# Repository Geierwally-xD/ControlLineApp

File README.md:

# ControlLineApp
Geierwally's stroke engine throttle control application for controlled line model planes

- Realizes full throttle control over control lines
- optional automatic flight position depended throttle control
- flight position sensor = MPU 6050 gyroscope accelerometer unit
- optional functions like retractable landing gear

- Hardware PCB design included, done with KiCad 8.0

- Full Software project included, done for Arduino Nano with VS Code and PlatformIO (optional Arduino IDE)
- See short video clip of position control and landing gear with landing light:
https://www.youtube.com/watch?v=91i4-DDLWDE

Geierwally's Verbrennungsmotor- Drosselvergasersteuerung für Fesselflugmodelle

- Drosselvergaser - Steuerung über Steuerdrähte mit optional automatischer Regelung über Fluglageerkennung
- Fluglagenerkennung über MPU 6050 Gyroskop Accelerometer - Einheit
- Optionale Funktionen wie Einziehfahrwerk

- Komplettes Hardware Platinenlayout enthalten, mit KiCad 8.0 entflochten

- Komplettes Software Projekt enthalten, für  Arduino Nano, entwickelt mit VS Code und PlatformIO (optional Arduino IDE)
- Kurzer Videoclip zeigt Regelung über Fluglage sowie Einziehfahrwerk und Landescheinwerfer:
https://www.youtube.com/watch?v=91i4-DDLWDE

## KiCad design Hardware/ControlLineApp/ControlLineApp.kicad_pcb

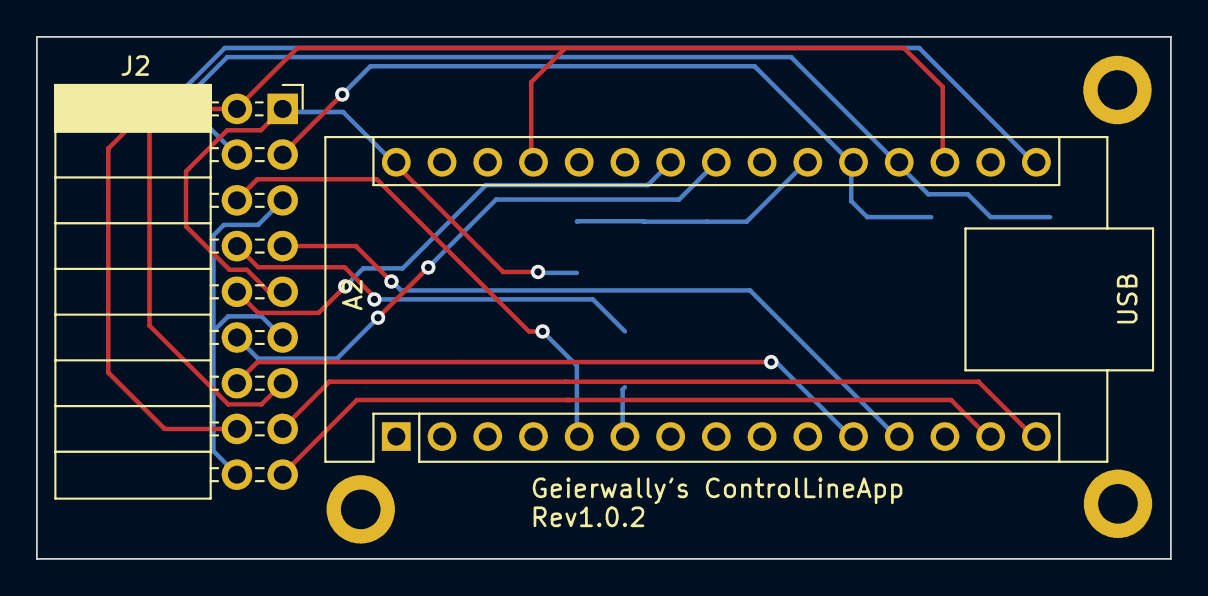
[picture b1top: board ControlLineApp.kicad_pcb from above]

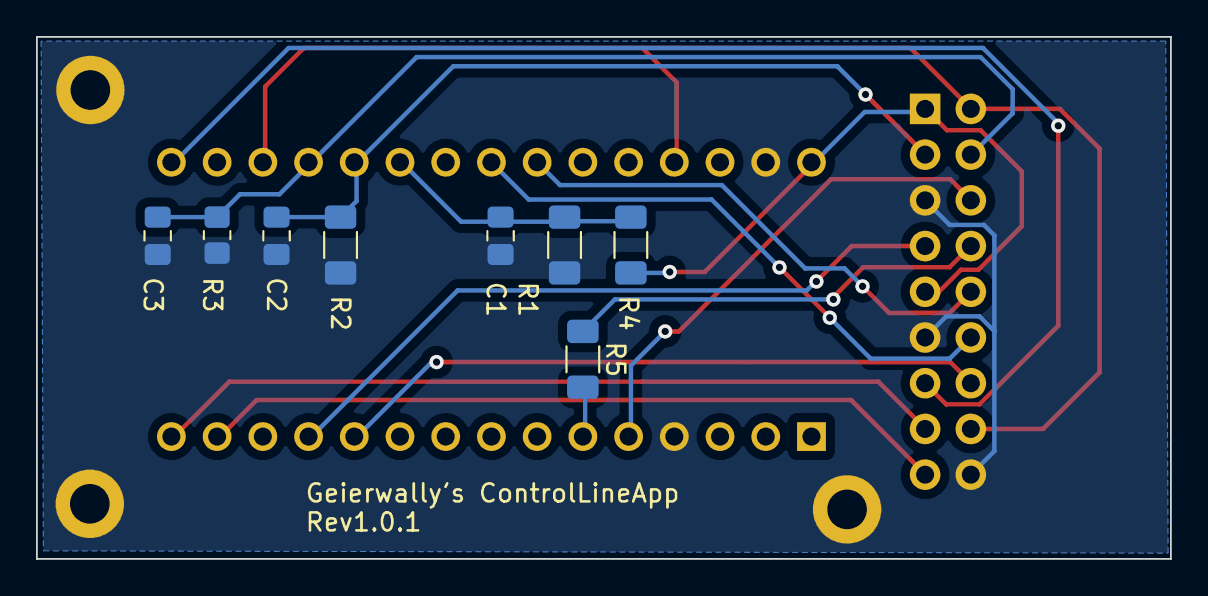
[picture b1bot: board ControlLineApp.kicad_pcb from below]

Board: 2 copper layers, 63.0 x 29.0 mm, 13 parts (8 on the bottom side), 16 nets.

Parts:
A2: Arduino Nano; Arduino_Nano
C1, C2, C3: 100n; C_0805_2012Metric_Pad1.18x1.45mm_HandSolder
H1, H2, H3: MountingHole_Pad; MountingHole_2.2mm_M2_DIN965_Pad
J2: Conn_02x09; PinSocket_2x09_P2.54mm_Horizontal
R1, R2: 1K; R_1206_3216Metric_Pad1.30x1.75mm_HandSolder
R3: 12K; R_0805_2012Metric_Pad1.20x1.40mm_HandSolder
R4: 820; R_1206_3216Metric_Pad1.30x1.75mm_HandSolder
R5: 470; R_1206_3216Metric_Pad1.30x1.75mm_HandSolder

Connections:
+5V: A2.18 (AREF), A2.27 (+5V), J2.2, J2.16
D8_FunctionPin3: A2.11 (D8), J2.14
D12_FunctionPin4: A2.15 (MISO), J2.15
D13_FunctionPin5: A2.16 (SCK), J2.13
GNDREF: A2.4 (GND), A2.29 (GND), C1.2, C2.2, C3.2, H1.1, H2.1, H3.1, J2.5, J2.11, J2.18, R1.1, R2.1, R3.1
LED_A: J2.8, R5.1
unnamed: A2.21 (A2), C1.1, R1.2, R4.2
unnamed: A2.6 (D3), R5.2
PWM RetractLandingGear: A2.14 (MOSI), J2.17
PWM Throttle: A2.12 (D9), J2.7
Poti10K: A2.19 (A0), C3.1, J2.4, R3.2
SCL: A2.24 (SCL/A5), J2.10
SDA: A2.23 (SDA/A4), J2.12
UserButton: A2.5 (D2), J2.6
VDD: A2.30 (VIN), J2.1, J2.9, R4.1
VPCell_1: A2.20 (A1), C2.1, J2.3, R2.2

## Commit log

2023-12-23 initial commit control line application V1.0.0
2023-12-26 PCB and schematic designed with KiCad 7.0
2023-12-31 PCB and schematic adapted with I²C interface, software implementation accelerometer gyroscope
2024-01-21 gyro flight feature implementation finished
2024-01-31 bugfixing
2024-02-04 md file and docu implemented
2024-02-04 md file adapted
2024-02-05 temporal folder MPU6050 deleted
2025-02-27 App extended with additional functions like retractable landing gear
2025-02-28 documentation of new features
2025-03-01 bugfix init endposition functiion servo
2025-03-02 bugfix voltage protection
